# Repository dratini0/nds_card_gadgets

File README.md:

# NDS card gadgets

A collection of bits and bobs, mostly exploiting the SPI bus of the DS/3DS cartridge slot.

## Devices
* `host_card`: A simple breakout cartridge that connects the cartridge slot to a ribbon cable
* `expansion_and_socket_card`: Another simple breakout, which exposes a mostly Arduino-compatible header, along with an extra header to attach a logic analyzer to, and an extra cartridge socket
* `hub75_extension`: A signal routing board to attach HUB75 LED panels in a variety of different topologies to the DS
* `usb_card`: Ever wondered what happened if you attached a MAX3421e to a DS? This.

## Todo:
* [ ] Re-layout the HUB75 board
* [ ] Add ESD diodes to the host card

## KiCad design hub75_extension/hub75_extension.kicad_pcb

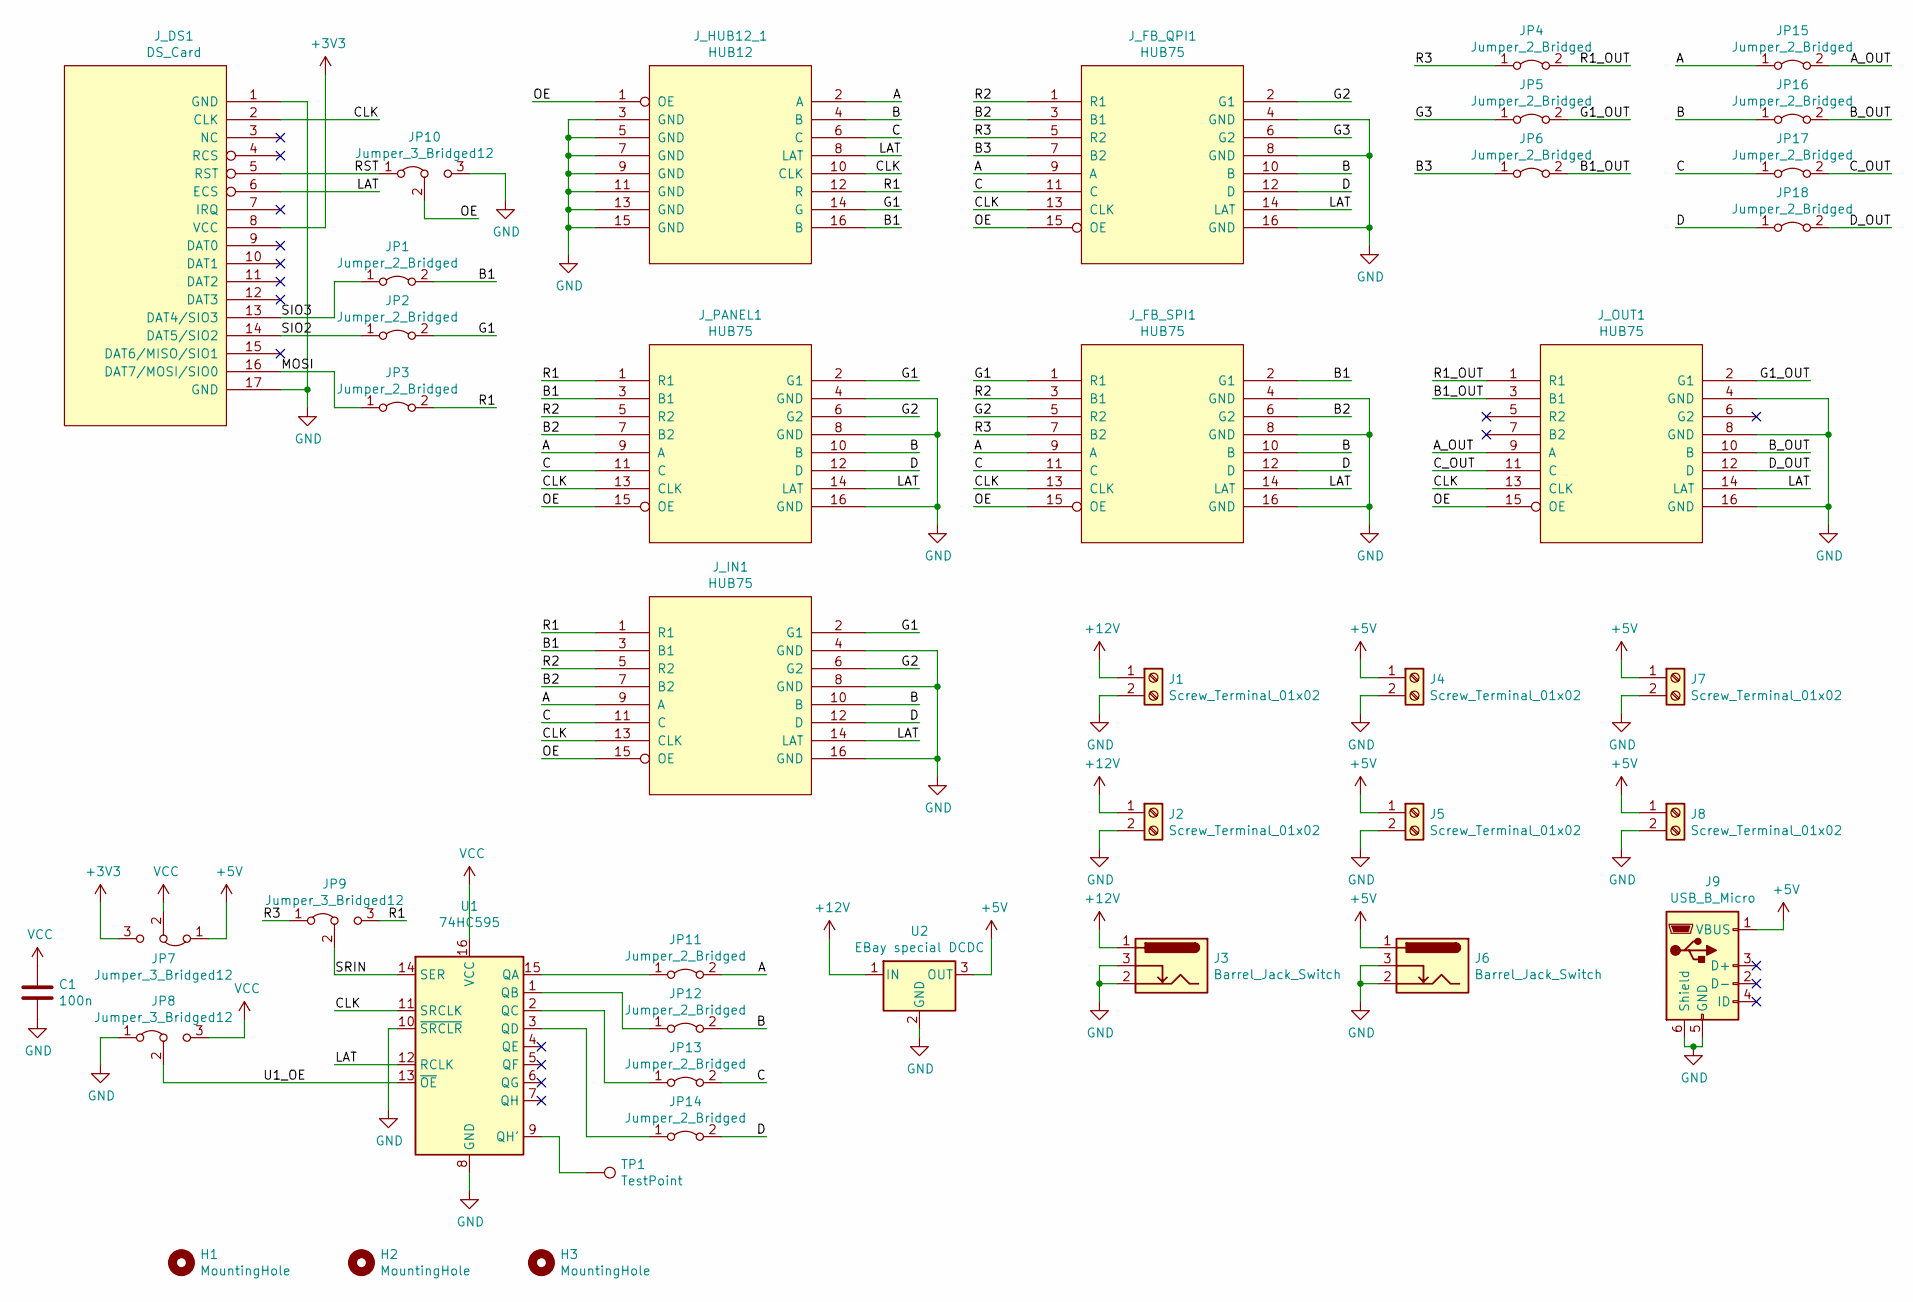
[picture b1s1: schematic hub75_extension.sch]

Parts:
C1: 100n; C_0603_1608Metric_Pad1.08x0.95mm_HandSolder; LCSC C14663
H1, H2, H3: MountingHole; JLC_TOOLING_HOLE
J1, J2, J4, J5, J7, J8: Screw_Terminal_01x02; TerminalBlock_bornier-2_P5.08mm
J3, J6: Barrel_Jack_Switch; BarrelJack_Horizontal
J9: USB_B_Micro; USB_Micro-B_Wuerth_629105150521
JP1, JP2, JP3, JP4, JP5, JP6, JP11, JP12, JP13, JP14, JP15, JP16, JP17, JP18: Jumper_2_Bridged; PinHeader_1x02_P2.54mm_Vertical
JP7, JP8, JP9, JP10: Jumper_3_Bridged12; PinHeader_1x03_P2.54mm_Vertical
J_DS1: DS_Card; IDC-Header_2x09_P2.54mm_Vertical
J_FB_QPI1: HUB75; IDC-Header_2x08_P2.54mm_Vertical
J_FB_SPI1: HUB75; IDC-Header_2x08_P2.54mm_Vertical
J_HUB12_1: HUB12; PinSocket_2x08_P2.54mm_Vertical
J_IN1: HUB75; IDC-Header_2x08_P2.54mm_Vertical
J_OUT1: HUB75; IDC-Header_2x08_P2.54mm_Vertical
J_PANEL1: HUB75; PinSocket_2x08_P2.54mm_Vertical
TP1: TestPoint; PinHeader_1x01_P2.54mm_Vertical
U1: 74HC595; SOIC-16_3.9x9.9mm_P1.27mm; LCSC C5947
U2: EBay special DCDC; ebay_special_dcdc

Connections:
+3V3: JP7.3 (B), J_DS1.8 (VCC)
+5V: J4.1, J5.1, J6.1, J7.1, J8.1, J9.1 (VBUS), JP7.1 (A), U2.3 (OUT)
+12V: J1.1, J2.1, J3.1, U2.1 (IN)
/A: JP11.2 (B), JP15.1 (A), J_FB_QPI1.9 (A), J_FB_SPI1.9 (A), J_HUB12_1.2 (A), J_IN1.9 (A), J_PANEL1.9 (A)
/A_OUT: JP15.2 (B), J_OUT1.9 (A)
/B: JP12.2 (B), JP16.1 (A), J_FB_QPI1.10 (B), J_FB_SPI1.10 (B), J_HUB12_1.4 (B), J_IN1.10 (B), J_PANEL1.10 (B)
/B1: JP1.2 (B), J_FB_SPI1.2 (G1), J_HUB12_1.16 (B), J_IN1.3 (B1), J_PANEL1.3 (B1)
/B1_OUT: JP6.2 (B), J_OUT1.3 (B1)
/B2: J_FB_QPI1.3 (B1), J_FB_SPI1.6 (G2), J_IN1.7 (B2), J_PANEL1.7 (B2)
/B3: JP6.1 (A), J_FB_QPI1.7 (B2)
/B_OUT: JP16.2 (B), J_OUT1.10 (B)
/C: JP13.2 (B), JP17.1 (A), J_FB_QPI1.11 (C), J_FB_SPI1.11 (C), J_HUB12_1.6 (C), J_IN1.11 (C), J_PANEL1.11 (C)
/CLK: J_DS1.2 (CLK), J_FB_QPI1.13 (CLK), J_FB_SPI1.13 (CLK), J_HUB12_1.10 (CLK), J_IN1.13 (CLK), J_OUT1.13 (CLK), J_PANEL1.13 (CLK), U1.11 (SRCLK)
/C_OUT: JP17.2 (B), J_OUT1.11 (C)
/D: JP14.2 (B), JP18.1 (A), J_FB_QPI1.12 (D), J_FB_SPI1.12 (D), J_IN1.12 (D), J_PANEL1.12 (D)
/D_OUT: JP18.2 (B), J_OUT1.12 (D)
/G1: JP2.2 (B), J_FB_SPI1.1 (R1), J_HUB12_1.14 (G), J_IN1.2 (G1), J_PANEL1.2 (G1)
/G1_OUT: JP5.2 (B), J_OUT1.2 (G1)
/G2: J_FB_QPI1.2 (G1), J_FB_SPI1.5 (R2), J_IN1.6 (G2), J_PANEL1.6 (G2)
/G3: JP5.1 (A), J_FB_QPI1.6 (G2)
/LAT: J_DS1.6 (ECS), J_FB_QPI1.14 (LAT), J_FB_SPI1.14 (LAT), J_HUB12_1.8 (LAT), J_IN1.14 (LAT), J_OUT1.14 (LAT), J_PANEL1.14 (LAT), U1.12 (RCLK)
/MOSI: JP3.1 (A), J_DS1.16 (DAT7/MOSI/SIO0)
/OE: JP10.2 (C), J_FB_QPI1.15 (OE), J_FB_SPI1.15 (OE), J_HUB12_1.1 (OE), J_IN1.15 (OE), J_OUT1.15 (OE), J_PANEL1.15 (OE)
/R1: JP3.2 (B), JP9.3 (B), J_HUB12_1.12 (R), J_IN1.1 (R1), J_PANEL1.1 (R1)
/R1_OUT: JP4.2 (B), J_OUT1.1 (R1)
/R2: J_FB_QPI1.1 (R1), J_FB_SPI1.3 (B1), J_IN1.5 (R2), J_PANEL1.5 (R2)
/R3: JP4.1 (A), JP9.1 (A), J_FB_QPI1.5 (R2), J_FB_SPI1.7 (B2)
/RST: JP10.1 (A), J_DS1.5 (RST)
/SIO2: JP2.1 (A), J_DS1.14 (DAT5/SIO2)
/SIO3: JP1.1 (A), J_DS1.13 (DAT4/SIO3)
/SRIN: JP9.2 (C), U1.14 (SER)
/U1_OE: JP8.2 (C), U1.13 (~OE)
GND: C1.2, J1.2, J2.2, J3.2, J3.3, J4.2, J5.2, J6.2, J6.3, J7.2, J8.2, J9.5 (GND), J9.6 (Shield), JP8.1 (A), JP10.3 (B), J_DS1.1 (GND), J_DS1.17 (GND), J_FB_QPI1.4 (GND), J_FB_QPI1.8 (GND), J_FB_QPI1.16 (GND), J_FB_SPI1.4 (GND), J_FB_SPI1.8 (GND), J_FB_SPI1.16 (GND), J_HUB12_1.3 (GND), J_HUB12_1.5 (GND), J_HUB12_1.7 (GND), J_HUB12_1.9 (GND), J_HUB12_1.11 (GND), J_HUB12_1.13 (GND), J_HUB12_1.15 (GND), J_IN1.4 (GND), J_IN1.8 (GND), J_IN1.16 (GND), J_OUT1.4 (GND), J_OUT1.8 (GND), J_OUT1.16 (GND), J_PANEL1.4 (GND), J_PANEL1.8 (GND), J_PANEL1.16 (GND), U1.8 (GND), U1.10 (~SRCLR), U2.2 (GND)
unnamed: JP11.1 (A), U1.15 (QA)
unnamed: JP12.1 (A), U1.1 (QB)
unnamed: JP13.1 (A), U1.2 (QC)
unnamed: JP14.1 (A), U1.3 (QD)
unnamed: TP1.1, U1.9 (QH')
VCC: C1.1, JP7.2 (C), JP8.3 (B), U1.16 (VCC)

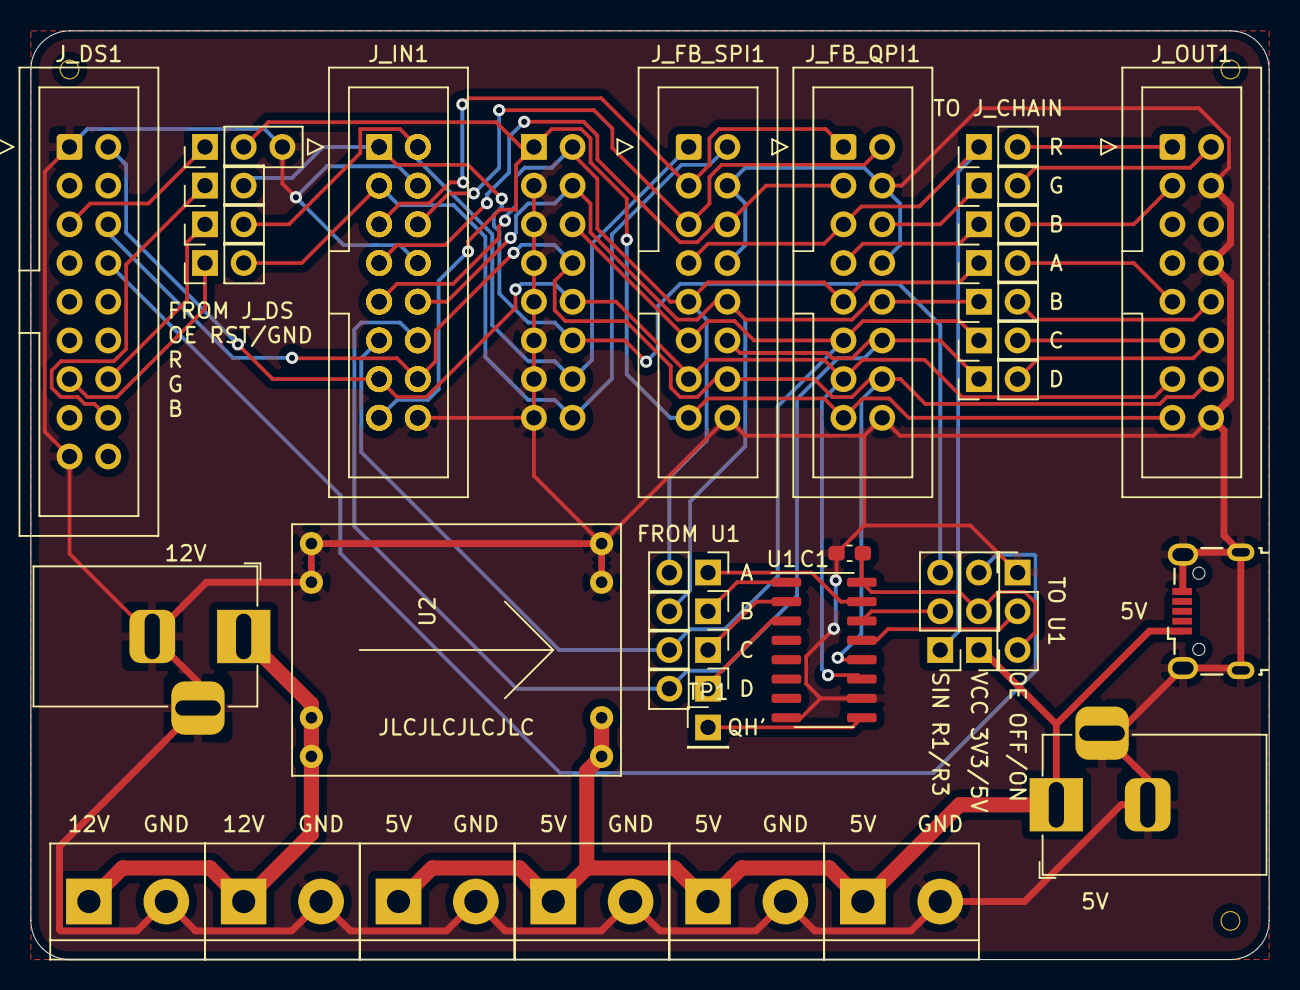
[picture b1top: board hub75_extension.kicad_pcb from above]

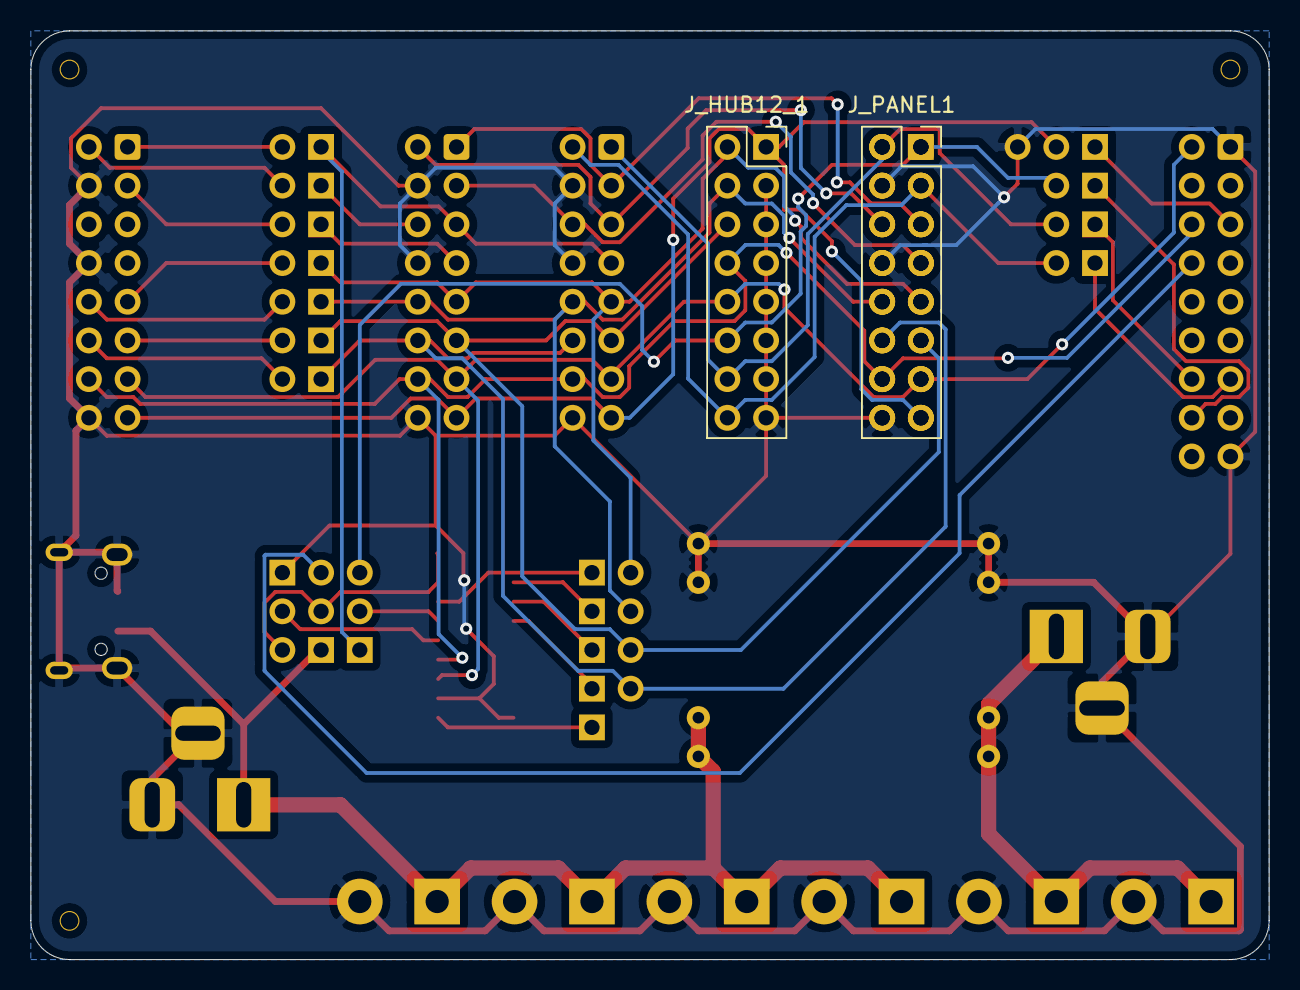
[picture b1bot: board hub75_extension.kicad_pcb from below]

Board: 2 copper layers, 81.3 x 61.0 mm, 41 parts (2 on the bottom side), 39 nets.

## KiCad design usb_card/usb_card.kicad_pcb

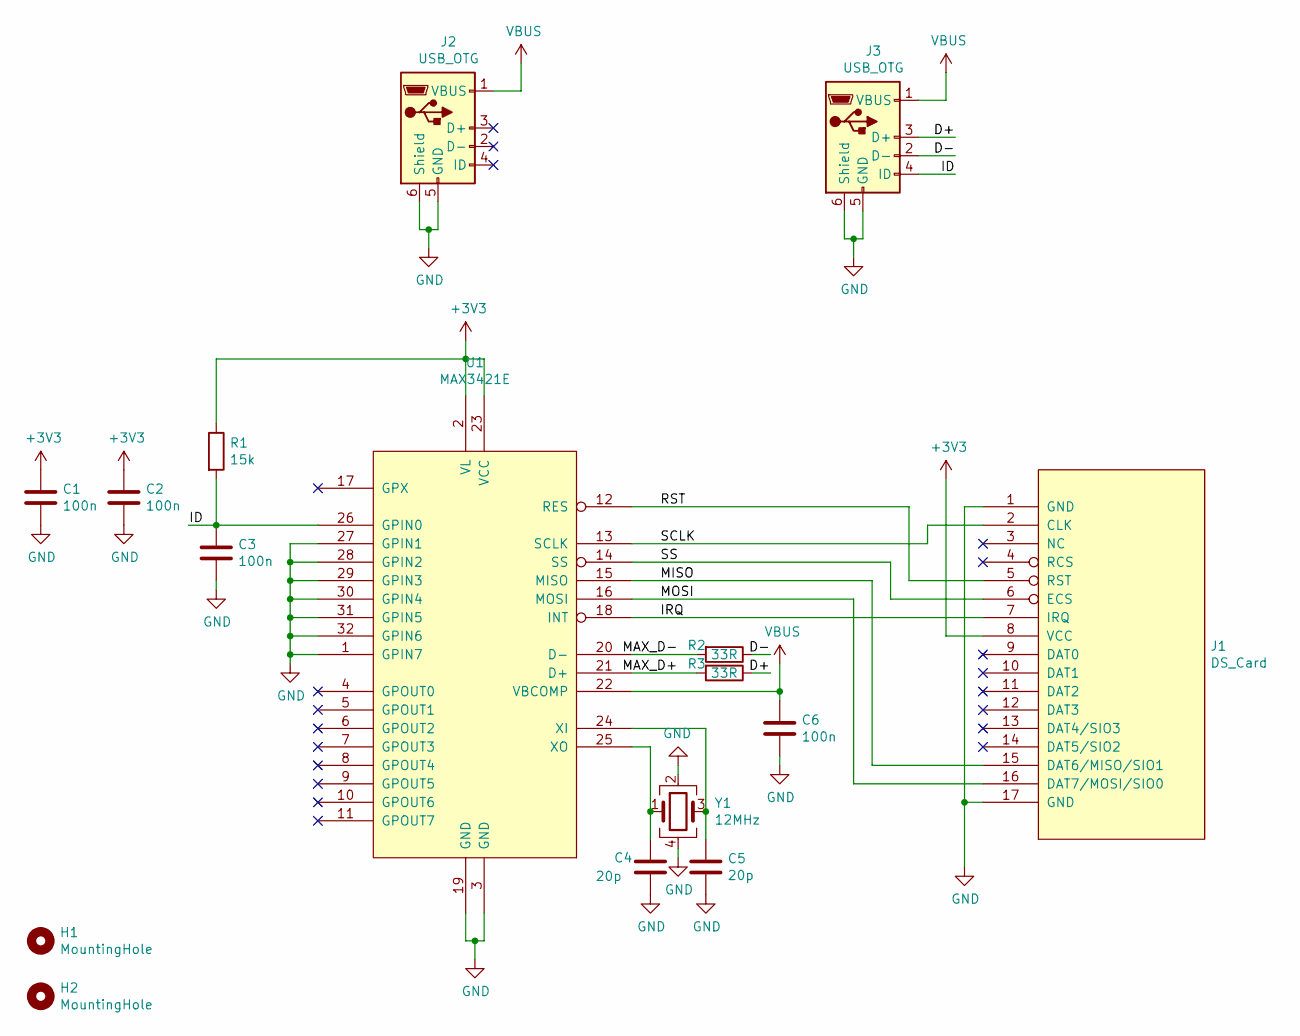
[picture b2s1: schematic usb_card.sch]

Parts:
C1, C2, C3, C6: 100n; C_0603_1608Metric; LCSC C14663
C4, C5: 20p; C_0603_1608Metric; LCSC C1648
H1, H2: MountingHole; JLC_TOOLING_HOLE
J1: DS_Card; ds_card
J2, J3: USB_OTG; USB_Micro-B_Wuerth_629105150521
R1: 15k; R_0603_1608Metric; LCSC C22809
R2, R3: 33R; R_0603_1608Metric; LCSC C23140
U1: MAX3421E; LQFP-32_5x5mm_P0.5mm; LCSC C45862
Y1: 12MHz; Crystal_SMD_3225-4Pin_3.2x2.5mm; LCSC C9002

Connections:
+3V3: C1.1, C2.1, J1.8 (VCC), R1.1, U1.2 (VL), U1.23 (VCC)
/D+: J3.3 (D+), R3.1
/D-: J3.2 (D-), R2.1
/ID: C3.1, J3.4 (ID), R1.2, U1.26 (GPIN0)
/IRQ: J1.7 (IRQ), U1.18 (INT)
/MAX_D+: R3.2, U1.21 (D+)
/MAX_D-: R2.2, U1.20 (D-)
/MISO: J1.15 (DAT6/MISO/SIO1), U1.15 (MISO)
/MOSI: J1.16 (DAT7/MOSI/SIO0), U1.16 (MOSI)
/RST: J1.5 (RST), U1.12 (RES)
/SCLK: J1.2 (CLK), U1.13 (SCLK)
/SS: J1.6 (ECS), U1.14 (SS)
GND: C1.2, C2.2, C3.2, C4.2, C5.2, C6.2, J1.1 (GND), J1.17 (GND), J2.5 (GND), J2.6 (Shield), J3.5 (GND), J3.6 (Shield), U1.1 (GPIN7), U1.3 (GND), U1.19 (GND), U1.27 (GPIN1), U1.28 (GPIN2), U1.29 (GPIN3), U1.30 (GPIN4), U1.31 (GPIN5), U1.32 (GPIN6), Y1.2, Y1.4
unnamed: C4.1, U1.25 (XO), Y1.1
unnamed: C5.1, U1.24 (XI), Y1.3
VBUS: C6.1, J2.1 (VBUS), J3.1 (VBUS), U1.22 (VBCOMP)

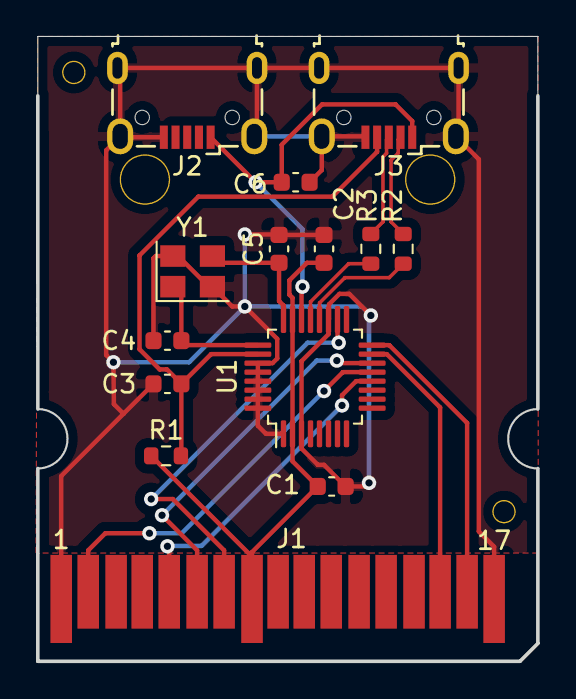
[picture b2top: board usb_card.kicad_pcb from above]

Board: 2 copper layers, 27.8 x 34.6 mm, 16 parts (0 on the bottom side), 16 nets.

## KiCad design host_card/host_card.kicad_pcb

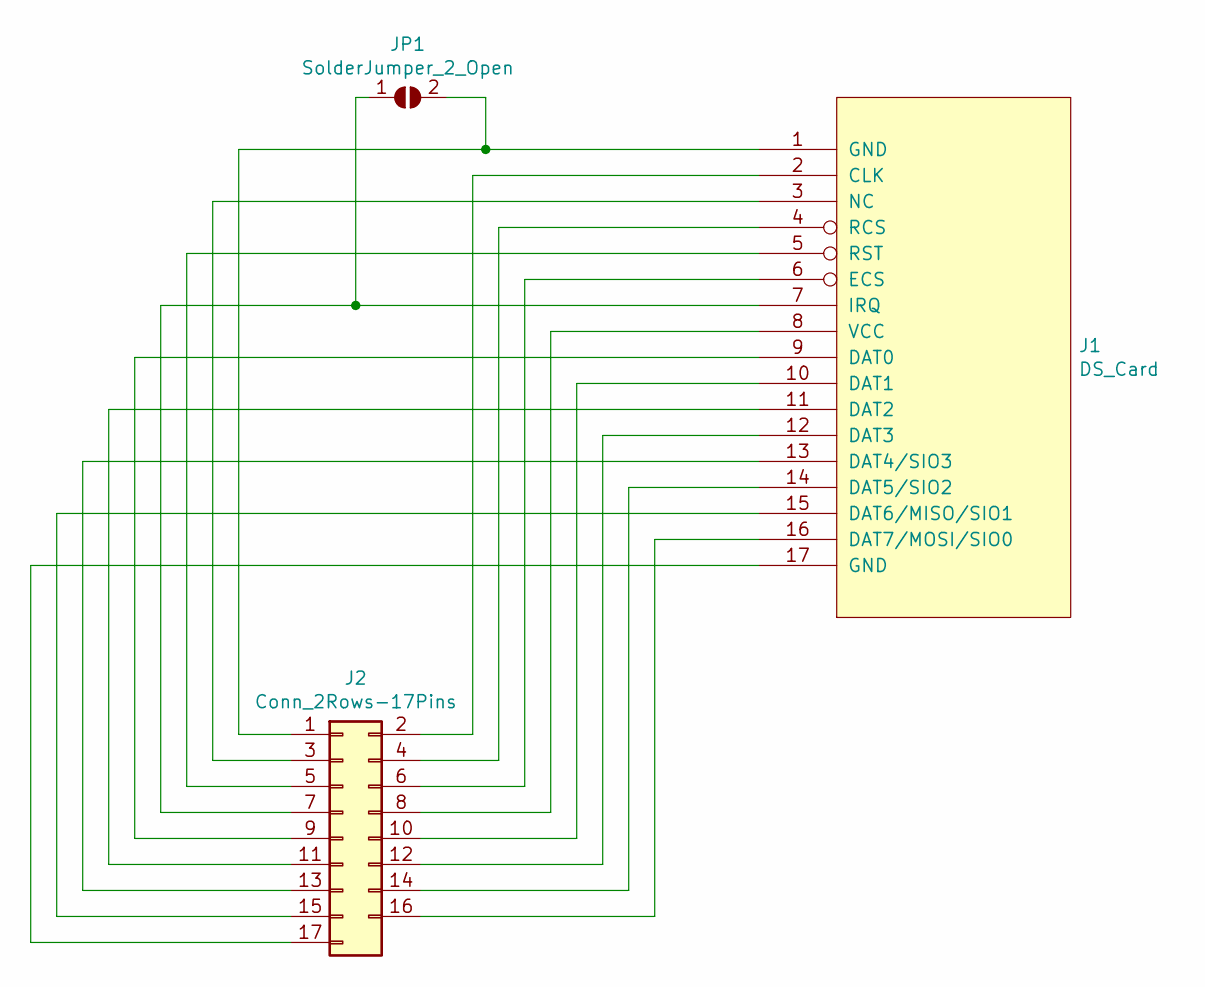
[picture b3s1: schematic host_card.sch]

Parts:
J1: DS_Card; ds_card
J2: Conn_2Rows-17Pins; PinHeader_2x09_P2.54mm_Vertical
JP1: SolderJumper_2_Open; SolderJumper-2_P1.3mm_Open_TrianglePad1.0x1.5mm

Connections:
unnamed: J1.1 (GND), J2.1, JP1.2 (B)
unnamed: J1.2 (CLK), J2.2
unnamed: J1.3 (NC), J2.3
unnamed: J1.4 (RCS), J2.4
unnamed: J1.5 (RST), J2.5
unnamed: J1.6 (ECS), J2.6
unnamed: J1.7 (IRQ), J2.7, JP1.1 (A)
unnamed: J1.8 (VCC), J2.8
unnamed: J1.9 (DAT0), J2.9
unnamed: J1.10 (DAT1), J2.10
unnamed: J1.11 (DAT2), J2.11
unnamed: J1.12 (DAT3), J2.12
unnamed: J1.13 (DAT4/SIO3), J2.13
unnamed: J1.14 (DAT5/SIO2), J2.14
unnamed: J1.15 (DAT6/MISO/SIO1), J2.15
unnamed: J1.16 (DAT7/MOSI/SIO0), J2.16
unnamed: J1.17 (GND), J2.17

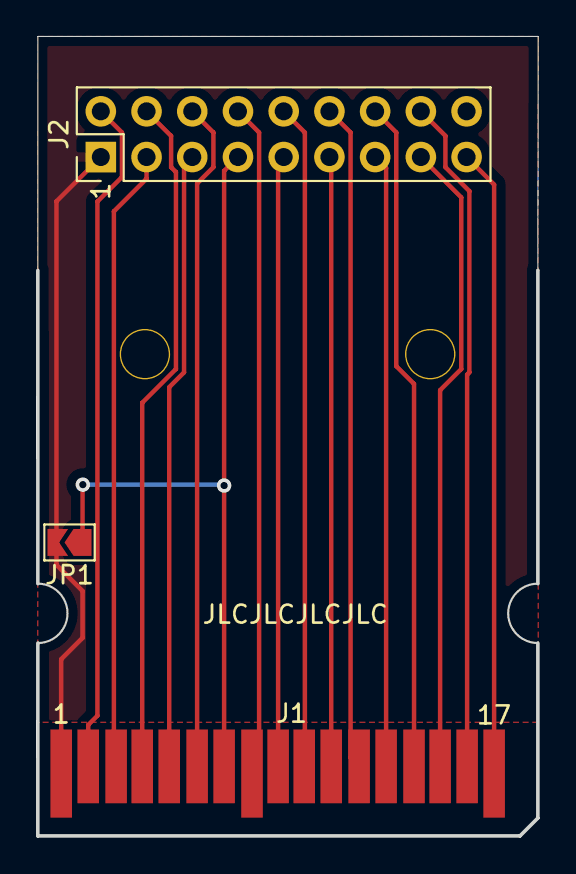
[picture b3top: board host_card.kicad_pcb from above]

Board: 2 copper layers, 27.8 x 44.3 mm, 3 parts (0 on the bottom side), 17 nets.

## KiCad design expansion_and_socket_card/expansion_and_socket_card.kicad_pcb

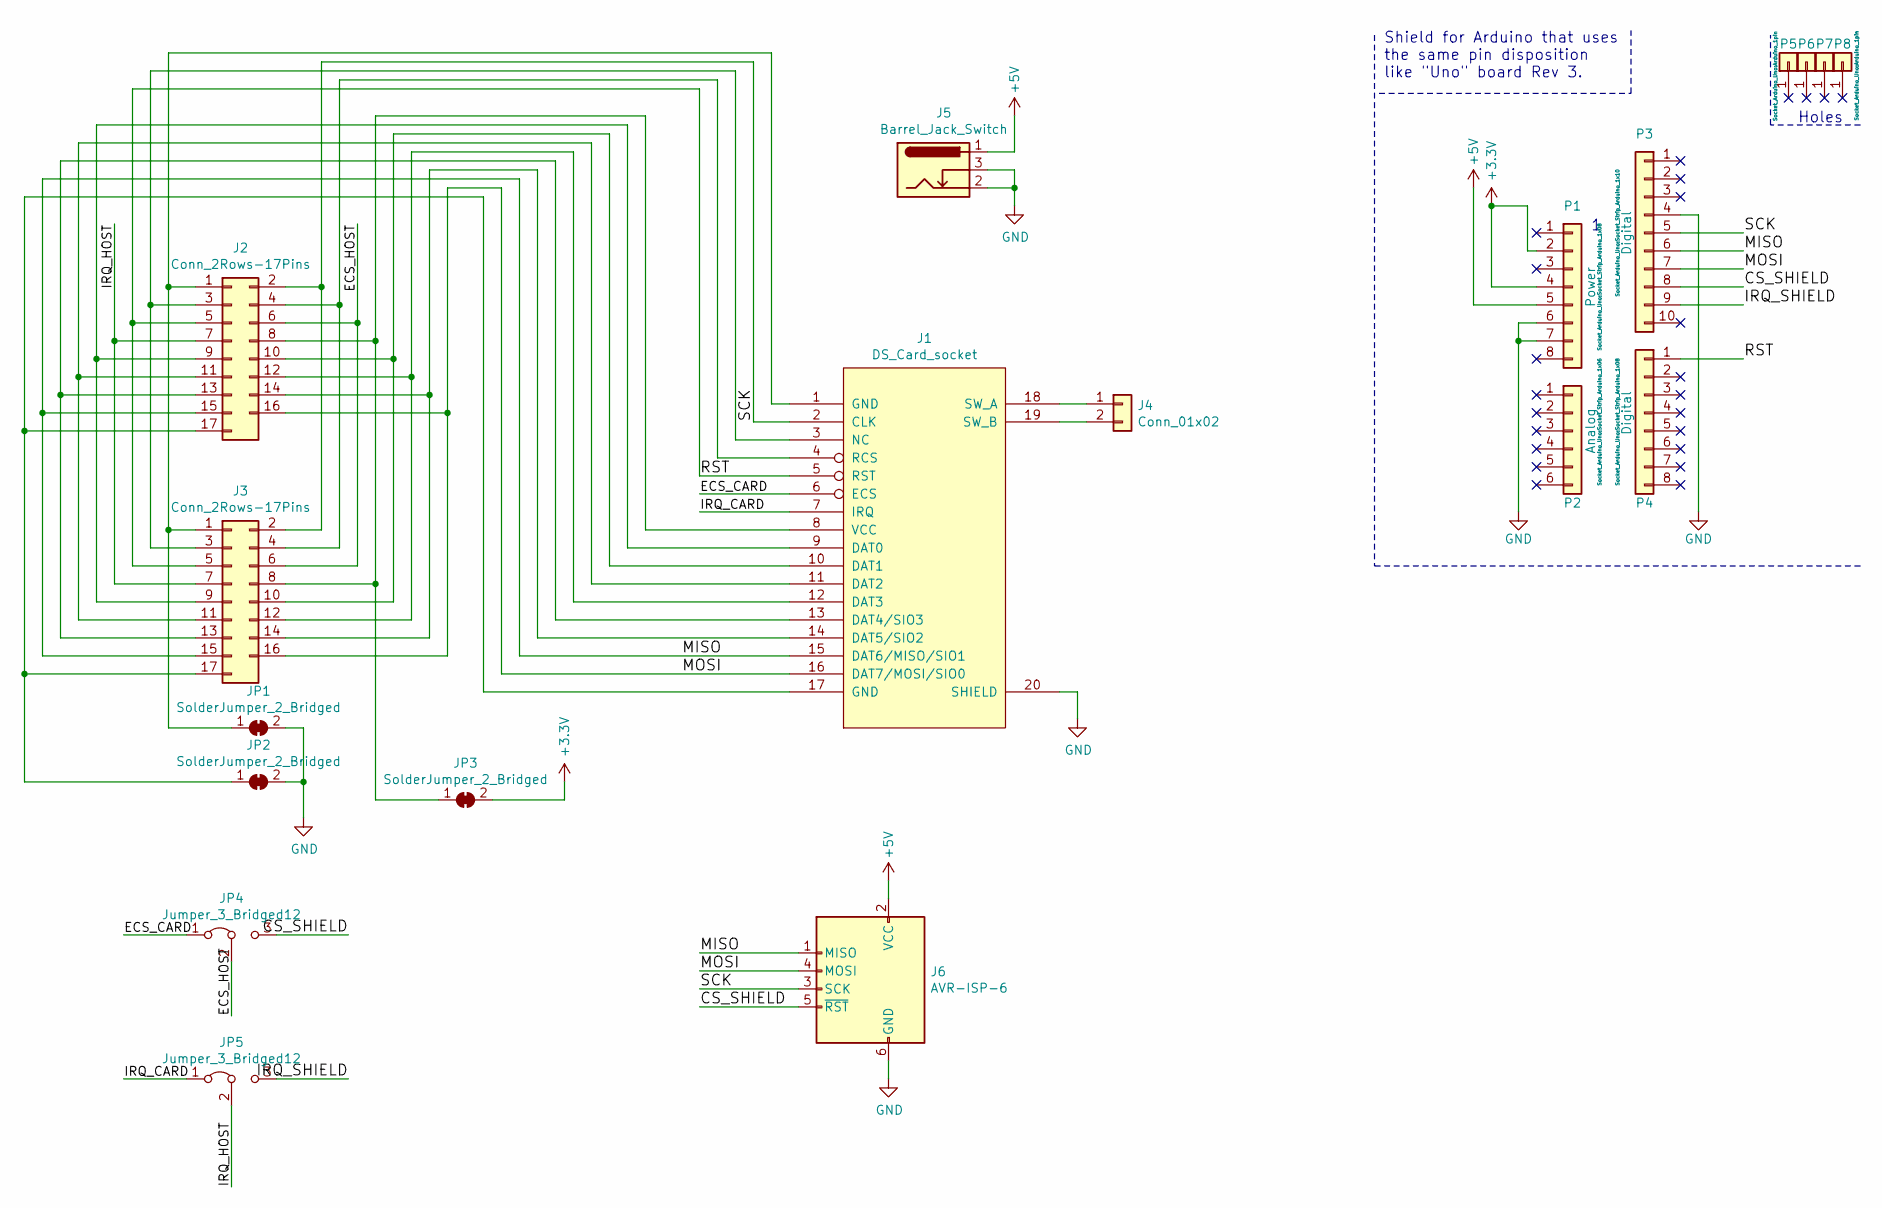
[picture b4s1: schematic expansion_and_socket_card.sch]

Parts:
J1: DS_Card_socket; 3ds_card_reader
J2, J3: Conn_2Rows-17Pins; PinHeader_2x09_P2.54mm_Vertical
J4: Conn_01x02; PinHeader_1x02_P2.54mm_Vertical
J5: Barrel_Jack_Switch; BarrelJack_Horizontal
J6: AVR-ISP-6; PinHeader_2x03_P2.54mm_Vertical
JP1, JP2, JP3: SolderJumper_2_Bridged; SolderJumper-2_P1.3mm_Bridged_Pad1.0x1.5mm
JP4, JP5: Jumper_3_Bridged12; PinHeader_1x03_P2.54mm_Vertical
P1: Power; Socket_Strip_Arduino_1x08
P2: Analog; Socket_Strip_Arduino_1x06
P3: Digital; Socket_Strip_Arduino_1x10
P4: Digital; Socket_Strip_Arduino_1x08
P5, P6, P7, P8: CONN_01X01; Arduino_1pin

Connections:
+3V3: JP3.2 (B), P1.2, P1.4
+5V: J5.1, J6.2 (VCC), P1.5
/CS_SHIELD: J6.5 (~RST), JP4.3 (B), P3.8
/ECS_CARD: J1.6 (ECS), JP4.1 (A)
/ECS_HOST: J2.6, J3.6, JP4.2 (C)
/IRQ_CARD: J1.7 (IRQ), JP5.1 (A)
/IRQ_HOST: J2.7, J3.7, JP5.2 (C)
/IRQ_SHIELD: JP5.3 (B), P3.9
/MISO: J1.15 (DAT6/MISO/SIO1), J2.15, J3.15, J6.1 (MISO), P3.6
/MOSI: J1.16 (DAT7/MOSI/SIO0), J2.16, J3.16, J6.4 (MOSI), P3.7
/RST: J1.5 (RST), J2.5, J3.5, P4.1
/SCK: J1.2 (CLK), J2.2, J3.2, J6.3 (SCK), P3.5
GND: J1.20 (SHIELD), J5.2, J5.3, J6.6 (GND), JP1.2 (B), JP2.2 (B), P1.6, P1.7, P3.4
unnamed: J1.1 (GND), J2.1, J3.1, JP1.1 (A)
unnamed: J1.3 (NC), J2.3, J3.3
unnamed: J1.4 (RCS), J2.4, J3.4
unnamed: J1.8 (VCC), J2.8, J3.8, JP3.1 (A)
unnamed: J1.9 (DAT0), J2.9, J3.9
unnamed: J1.10 (DAT1), J2.10, J3.10
unnamed: J1.11 (DAT2), J2.11, J3.11
unnamed: J1.12 (DAT3), J2.12, J3.12
unnamed: J1.13 (DAT4/SIO3), J2.13, J3.13
unnamed: J1.14 (DAT5/SIO2), J2.14, J3.14
unnamed: J1.17 (GND), J2.17, J3.17, JP2.1 (A)
unnamed: J1.18 (SW_A), J4.1
unnamed: J1.19 (SW_B), J4.2

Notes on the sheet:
Holes
Shield for Arduino that uses the same pin disposition like "Uno" board Rev 3.

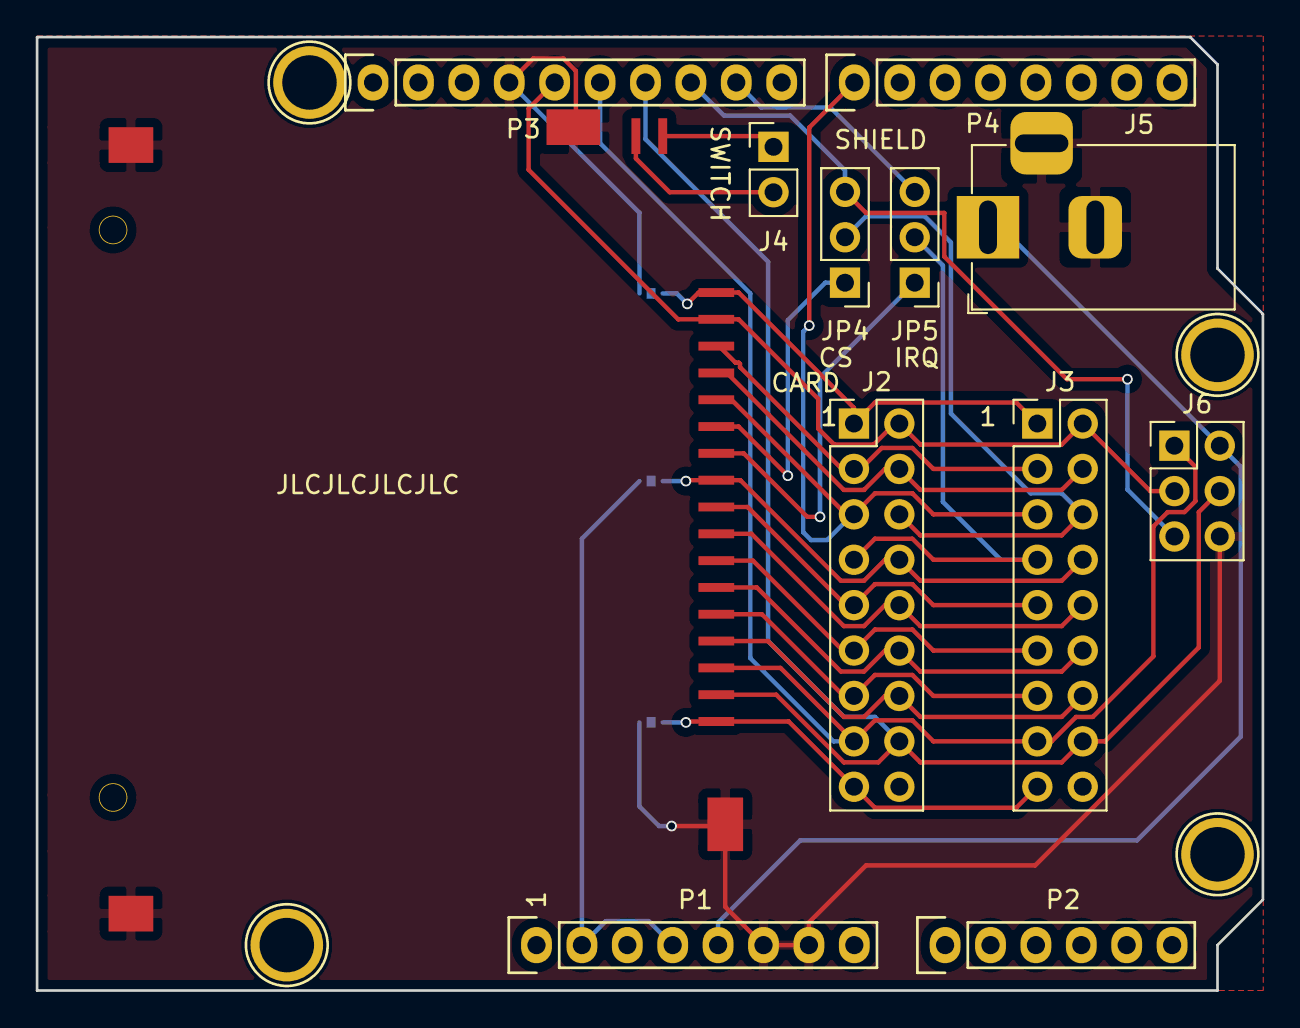
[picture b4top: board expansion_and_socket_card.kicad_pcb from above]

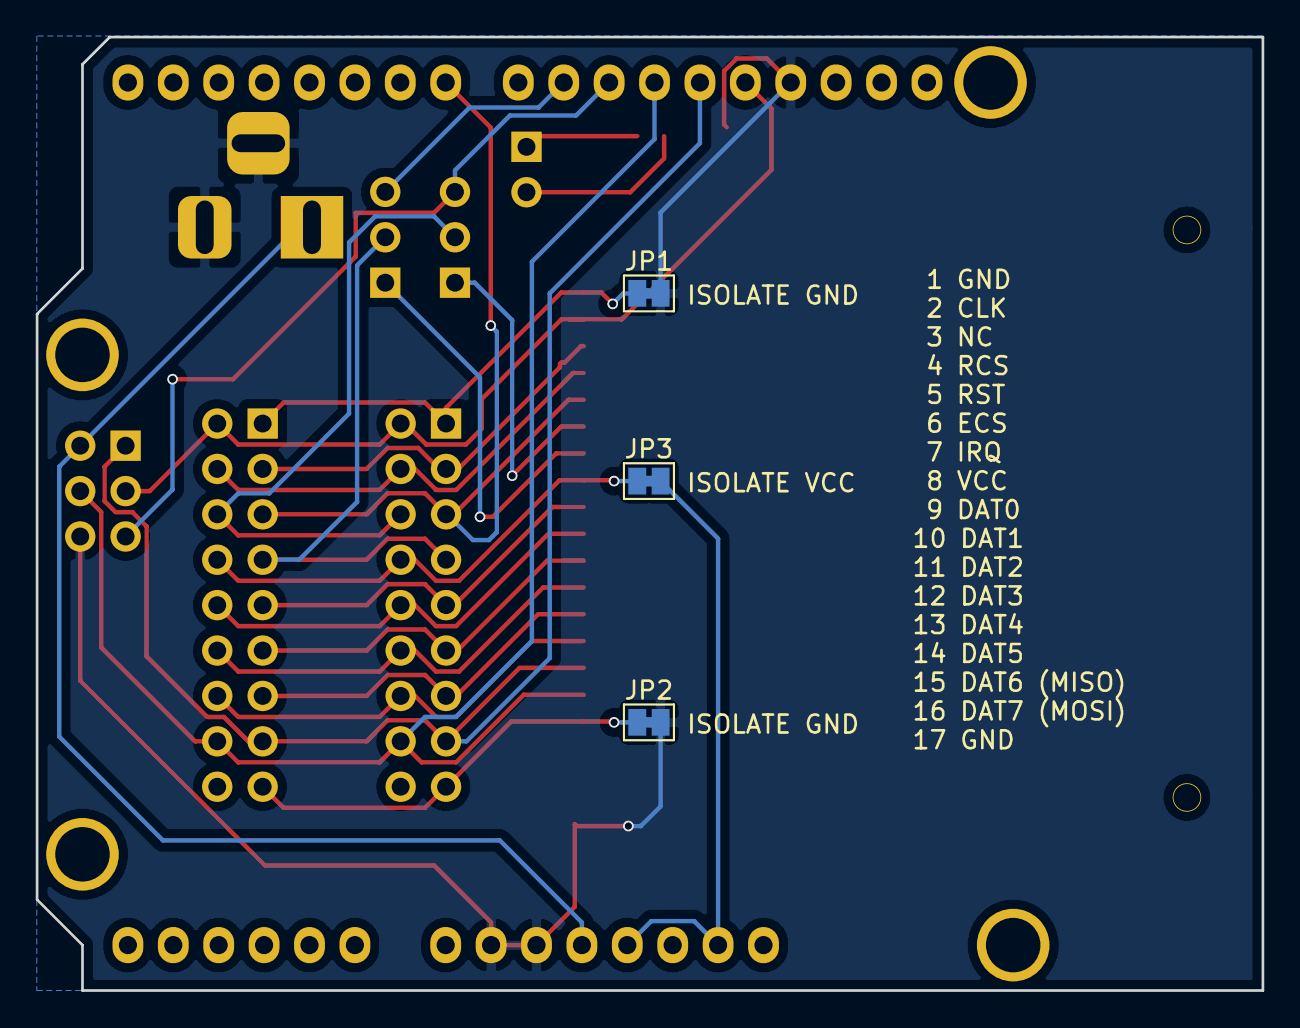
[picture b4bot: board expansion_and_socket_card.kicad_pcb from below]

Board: 2 copper layers, 68.6 x 53.3 mm, 19 parts (3 on the bottom side), 26 nets.

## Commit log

2020-12-21 initial commit (I didn't bother before)
2020-12-21 Fix missing GND connection in USB card
2020-12-21 Schematic improvements for the HUB75 board
2020-12-21 Update HUB75 board with new netlist
2020-12-28 Giant schematic update on the HUB75 extension
2020-12-28 Oops
2020-12-28 Add some spare footprints, just in case
2020-12-28 Fix HUB12 Oopsie, add support for E line on HUB75
2020-12-28 Add another option for OE, coming from the sreg
2020-12-28 Replace one of the hidden +5V line with GND because that should be low Z
2020-12-28 Refactor HUB75 connectors to their own sheet
2020-12-28 Forgot to renumber the new sheet
2020-12-28 Yeah, just renumber the entire thing...
2021-04-04 Readme + license
